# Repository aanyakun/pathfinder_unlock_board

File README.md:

# pathfinder_unlock_board
This is a small unlock-sequence-based controller board using Seed Studio XIAO RP2040

# PCB Preview!

# Schematic Preview!

# PCB Wiring Preview!

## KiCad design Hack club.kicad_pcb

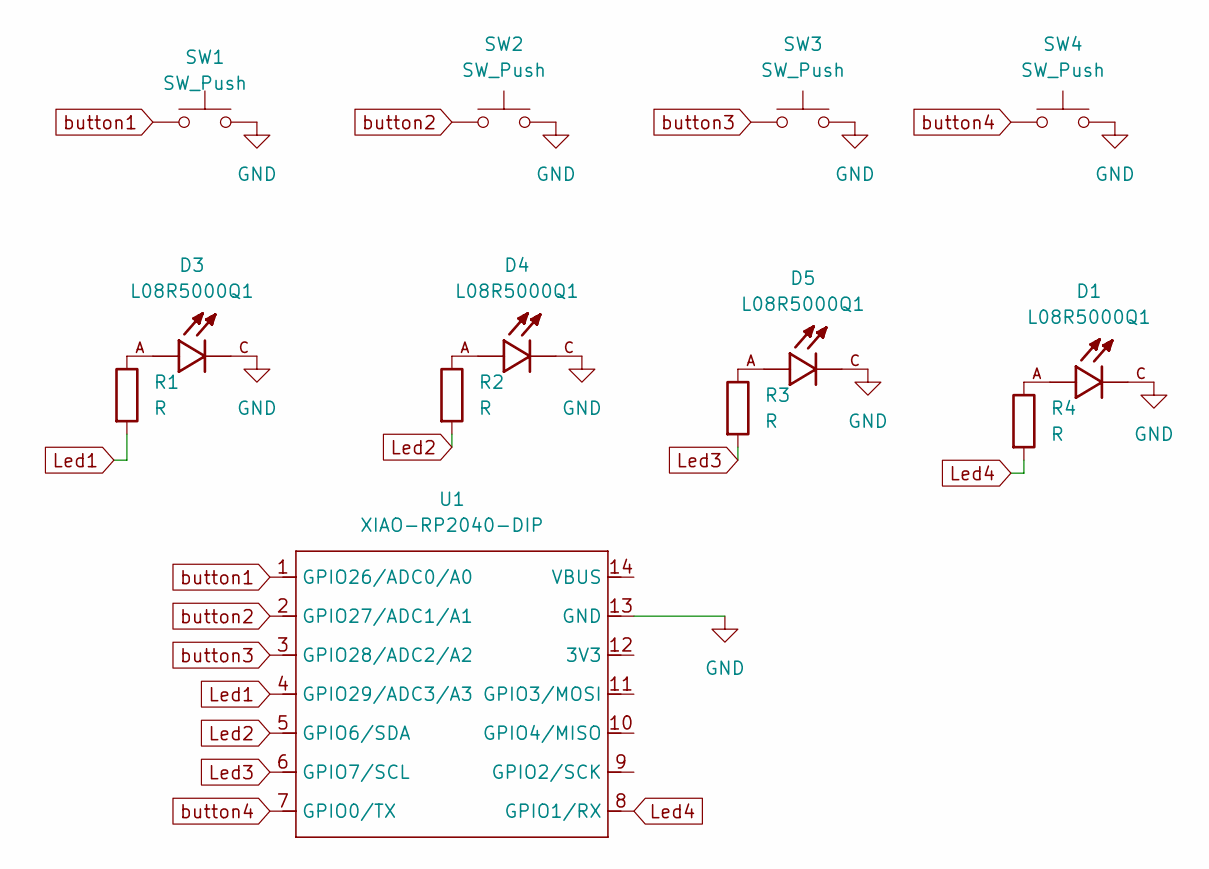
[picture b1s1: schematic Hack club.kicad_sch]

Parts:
D1, D3, D4, D5: L08R5000Q1; LEDRD254W57D500H1070; PARTREV NA
R1, R2, R3, R4: R; R_Axial_DIN0204_L3.6mm_D1.6mm_P5.08mm_Horizontal
SW1, SW2, SW3, SW4: SW_Push; SW_Cherry_MX_1.00u_PCB
U1: XIAO-RP2040-DIP

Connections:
GND: D1.C, D3.C, D4.C, D5.C, SW1.2, SW2.2, SW3.2, SW4.2, U1.13 (GND)
Led1: R1.2, U1.4 (GPIO29/ADC3/A3)
Led2: R2.2, U1.5 (GPIO6/SDA)
Led3: R3.2, U1.6 (GPIO7/SCL)
Led4: R4.2, U1.8 (GPIO1/RX)
unnamed: D1.A, R4.1
unnamed: D3.A, R1.1
unnamed: D4.A, R2.1
unnamed: D5.A, R3.1
button1: SW1.1, U1.1 (GPIO26/ADC0/A0)
button2: SW2.1, U1.2 (GPIO27/ADC1/A1)
button3: SW3.1, U1.3 (GPIO28/ADC2/A2)
button4: SW4.1, U1.7 (GPIO0/TX)

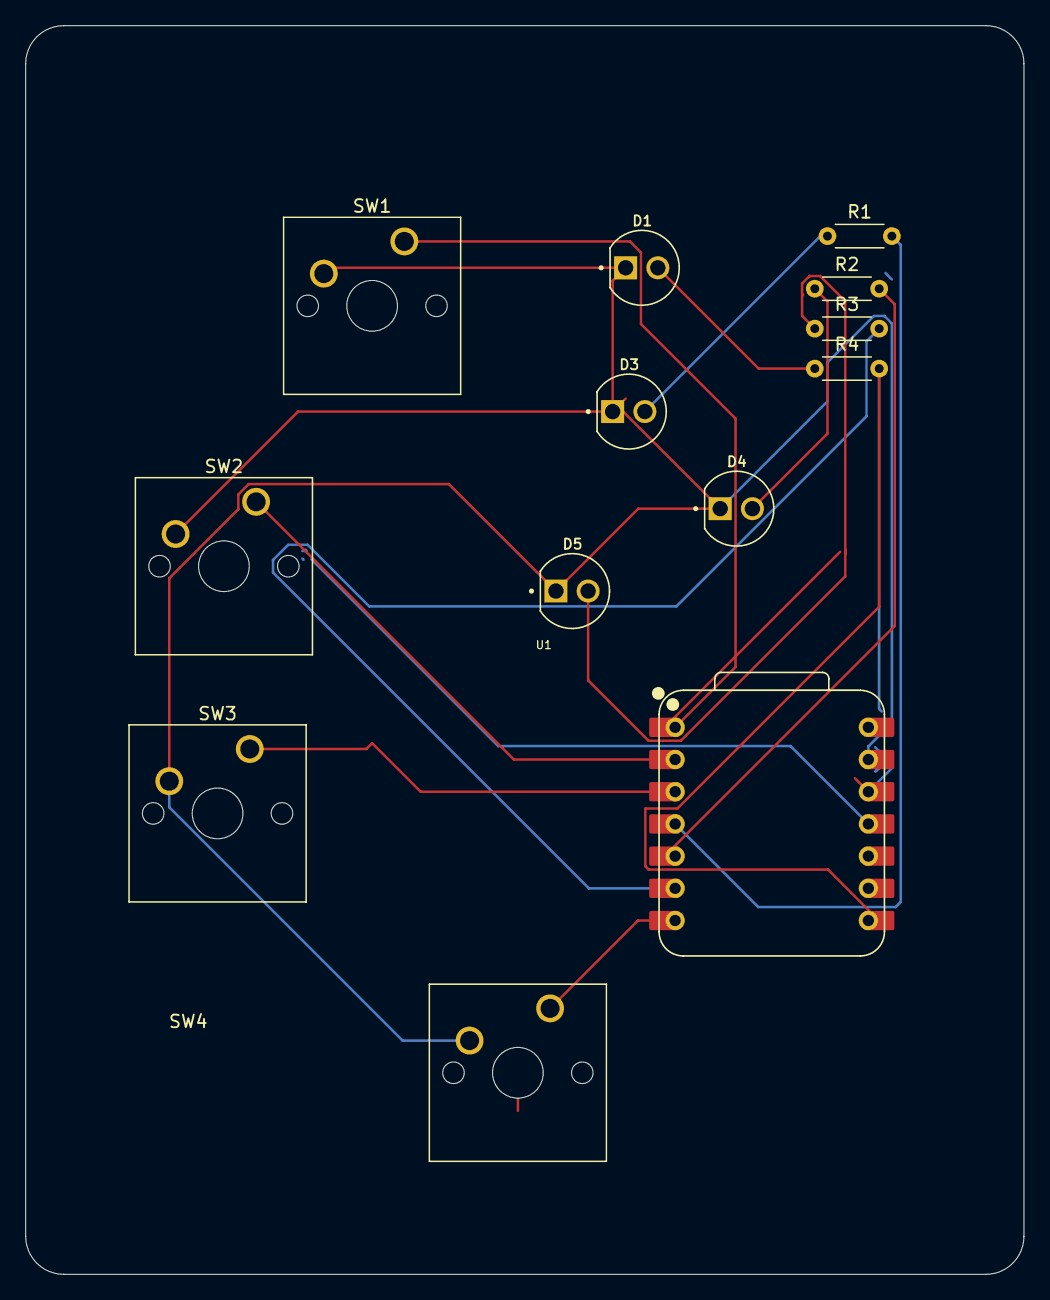
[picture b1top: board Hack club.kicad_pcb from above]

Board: 2 copper layers, 78.8 x 98.5 mm, 13 parts (0 on the bottom side), 13 nets.

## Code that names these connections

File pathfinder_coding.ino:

//I customized my firmware by adding a secret 3 2 1 unlock sequence. How it works is if you press buttons 3, then 2, then 1 in order in 5 seconds, LED2 lights up!!

int BUT1 = D0;
int BUT2 = D1;
int BUT3 = D2;

int LED1 = D3;
int LED2 = D4;
int LED3 = D5;

long but1time;
long but2time;
long but3time = 0;

int unlockState = 0;
int unlockStart = 0;

void setup() {
  pinMode(BUT1, INPUT);
  pinMode(BUT2, INPUT);
  pinMode(BUT3, INPUT);

  pinMode(LED1, OUTPUT);
  pinMode(LED2, OUTPUT);
  pinMode(LED3, OUTPUT);

  long startTime = millis();
}

void loop() {
  // Button 3!
  if (digitalRead(BUT3) == HIGH) {
    if (unlockState == 0) {
      unlockState = 1;
      unlockStart = millis();
    }
    but3time++;
  } else {
    but3time = 0;
  }

  // Button 2!
  if (digitalRead(BUT2) == HIGH) {
    but2time = millis();
    if (unlockState == 1 && millis() - unlockStart <= 5000) {
      unlockState = 2;
    } else {
      unlockState = 0;
    }
  }

  // Button 1!
  if (digitalRead(BUT1) == HIGH) {
    but1time = millis();
    digitalWrite(LED1, HIGH);

    if (unlockState == 2 && millis() - unlockStart <= 5000) {
      unlockState = 3;
    } else {
      unlockState = 0;
    }
  } else {
    digitalWrite(LED1, LOW);
  }

  
  if (abs(but2time - but1time) <= 2000 && unlockState == 3) {
    digitalWrite(LED2, HIGH);
  } else {
    digitalWrite(LED2, LOW);
  }

  if (but3time >= 800) {
    digitalWrite(LED3, HIGH);
  } else {
    digitalWrite(LED3, LOW);
  }
}

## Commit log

2025-07-05 Add files via upload
    PathFinder PCB Project files and firmware
